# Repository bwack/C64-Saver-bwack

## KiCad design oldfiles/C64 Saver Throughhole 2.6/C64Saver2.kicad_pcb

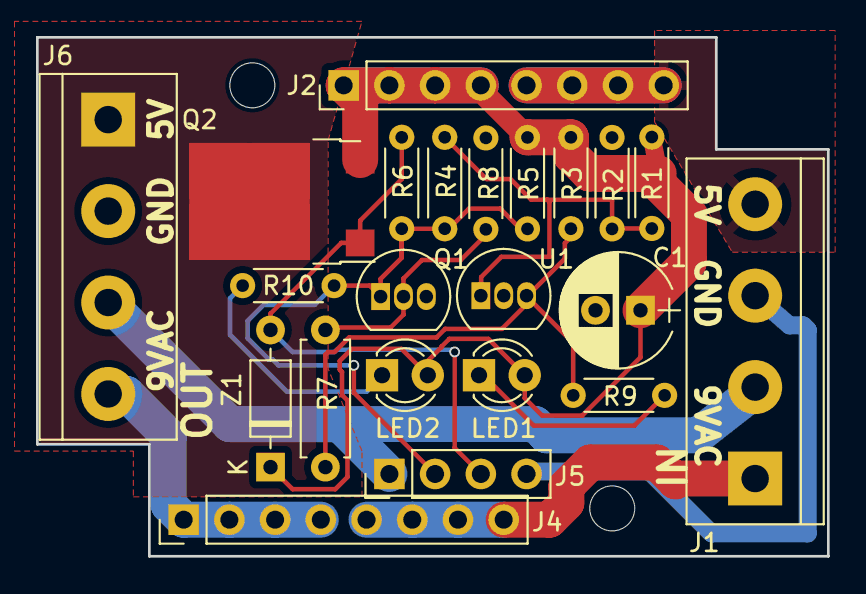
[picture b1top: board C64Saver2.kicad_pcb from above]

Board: 2 copper layers, 43.9 x 28.8 mm, 24 parts (0 on the bottom side), 14 nets.

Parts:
C1: 47uF; CP_Radial_D6.3mm_P2.50mm
J1, J6: Conn_01x04; TerminalBlock_bornier-4_P5.08mm
J2, J4: Conn_01x08; Pin_Header_Straight_1x08_Pitch2.54mm
J5: Conn_01x04; Pin_Header_Straight_1x04_Pitch2.54mm
LED1: 3mm RED; LED_D3.0mm
LED2: 3mm GREEN; LED_D3.0mm
MK1, MK2: Mounting_Hole; MountingHole_2.5mm
Q1: BC547; TO-92_Inline
Q2: IRFR5305; ATPAK-2
R1: 3k9 1%; R_Axial_DIN0204_L3.6mm_D1.6mm_P5.08mm_Horizontal
R2: 3k3 1%; R_Axial_DIN0204_L3.6mm_D1.6mm_P5.08mm_Horizontal
R3, R5: 3k3; R_Axial_DIN0204_L3.6mm_D1.6mm_P5.08mm_Horizontal
R4: 330k; R_Axial_DIN0204_L3.6mm_D1.6mm_P5.08mm_Horizontal
R6: 3k9; R_Axial_DIN0204_L3.6mm_D1.6mm_P5.08mm_Horizontal
R7: 33k; R_Axial_DIN0207_L6.3mm_D2.5mm_P7.62mm_Horizontal
R8: 10k; R_Axial_DIN0204_L3.6mm_D1.6mm_P5.08mm_Horizontal
R9, R10: 1k; R_Axial_DIN0204_L3.6mm_D1.6mm_P5.08mm_Horizontal
U1: TL431LP; TO-92_Inline
Z1: 6V8; D_DO-35_SOD27_P7.62mm_Horizontal

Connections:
/5V_SAFE: J6.1, Q2.2 (D)
/9VAC1: J1.1, J4.5, J4.6, J4.7, J4.8
/9VAC1': J4.1, J4.2, J4.3, J4.4, J6.4
/9VAC2: J1.2, J5.1, J6.3
/NGATE: Q1.2 (B), R7.2, R8.1
/SENSE: R1.2, R2.1, R4.1, U1.1 (REF)
/VCC1+: J1.4, J2.5, J2.6, J2.7, J2.8
/VCC1-: C1.1, J2.1, J2.2, J2.3, J2.4, LED1.2 (A), LED2.2 (A), Q2.3 (S), R1.1, R3.1, R5.1, Z1.1 (K)
GND: C1.2, J1.3, J5.4, J6.2, Q1.3 (E), R2.2, R8.2, U1.2 (A)
unnamed: LED1.1 (K), R9.1
unnamed: LED2.1 (K), R10.1
unnamed: R3.2, R7.1, R9.2, U1.3 (K)
OVERVOLTAGE: J5.2, Q1.1 (C), R4.2, R5.2, R6.2, R10.2
PGATE: J5.3, Q2.1 (G), R6.1, Z1.2 (A)

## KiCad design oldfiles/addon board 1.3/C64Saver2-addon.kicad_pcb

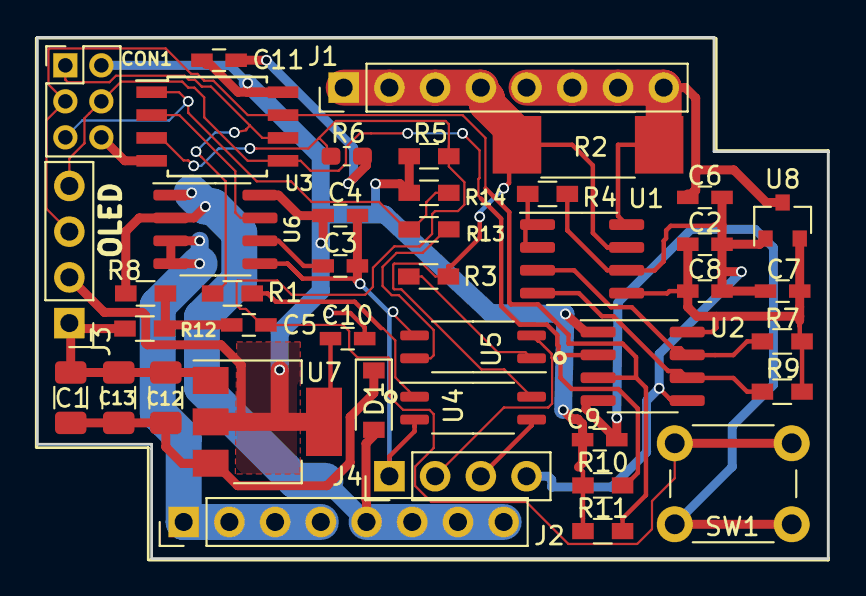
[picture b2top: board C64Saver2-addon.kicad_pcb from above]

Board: 2 copper layers, 43.9 x 29.0 mm, 42 parts (0 on the bottom side), 25 nets.

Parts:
C1, C12, C13: 47uF; C_1206_3216Metric
C2, C5, C8, C9, C11: 100n; C_0603_HandSoldering
C3, C6, C7, C10: 1u; C_0603_HandSoldering
C4: 100nF; C_0603_HandSoldering
CON1: AVR-ISP-6; Pin_Header_Straight_2x03_Pitch2.00mm
D1: Dotec SL1G; D_SOD-123
J1, J2: Conn_01x08_Female; Pin_Header_Straight_1x08_Pitch2.54mm
J3: OLED_128x32_Conn_01x04_Male; Pin_Header_Straight_1x04_Pitch2.54mm
J4: Conn_01x04_Female; Pin_Header_Straight_1x04_Pitch2.54mm
R1, R3: 560; R_0603_HandSoldering
R2: 0R1; R_2512_HandSoldering
R4: 10K; R_0603_HandSoldering
R5: 470k; R_0603_HandSoldering
R6: 470k; R_0603_1608Metric_Pad1.05x0.95mm_HandSolder
R7, R8, R9, R10, R11: 4k7; R_0603_HandSoldering
R12: 470; R_0603_HandSoldering
R13: 10k; R_0603_HandSoldering
R14: 1k; R_0603_HandSoldering
SW1: SW_Push; SW_PUSH_6mm_h13mm
U1: INA219xIDR-SOIC; SOIC-8_3.9x4.9mm_P1.27mm
U2: ISO1541D; SOIC-8_3.9x4.9mm_P1.27mm
U3: ATTINY85-20SU; SOIJ-8_5.3x5.3mm_P1.27mm
U4, U5: ACPL-217-50DE; SOIC-4_4.55x2.6mm_P1.27mm
U6: ACS712; SOIC-8_3.9x4.9mm_P1.27mm
U7: MCP1703; SOT-223-3_TabPin2
U8: MCP1703; SOT-23

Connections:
+5V: C4.2, C9.1, C10.2, C11.2, CON1.2, J3.2, R5.2, R10.2, R11.2, R14.2, U2.1, U3.8, U6.8, U7.2
/9VAC1+: D1.2, J2.5, J2.6, J2.7, J2.8, R8.2, U6.1, U6.2
/9VAC1-: J2.1, J2.2, J2.3, J2.4, U6.3, U6.4
/#OVERVOLTAGE: CON1.5, R13.1, R14.1, U3.1
/FILTER: C3.2, U6.6
/HOLD: R1.2, U4.1
/HOLD_: CON1.1, R1.1, U3.6
/SCL1: CON1.3, J3.3, R11.1, U2.3, U3.7
/SCL2: R9.1, U1.4, U2.6
/SDA1: CON1.4, J3.4, R10.1, U2.2, U3.5
/SDA2: R7.1, U1.3, U2.7
/SENSE_ACCUR: U3.2, U6.7
/SENSE_VAC: C5.2, R5.1, R6.2, SW1.2, U3.3
/VDD2: C2.1, C7.2, C8.1, R7.2, R9.2, U1.5, U2.8, U8.2
/VIN+: C6.2, J1.5, J1.6, J1.7, J1.8, R2.2, U1.8, U8.3
GND: C1.2, C3.1, C4.1, C9.2, C10.1, C11.1, C12.2, C13.2, CON1.6, J3.1, J4.1, R6.1, R12.1, SW1.1, U2.4, U3.4, U4.2, U5.3, U6.5, U7.1
GNDD: C2.2, C6.1, C7.1, C8.2, J4.4, R4.1, U1.6, U2.5, U8.1
unnamed: C1.1, C12.1, C13.1, D1.1, U7.3
unnamed: C5.1, R8.1, R12.2
unnamed: R3.1, U5.1
unnamed: R4.2, U1.1, U1.2
unnamed: R13.2, U5.4
OVERVOLTAGE: J4.2, U5.2
PGATE: J4.3, U4.3
VIN-: J1.1, J1.2, J1.3, J1.4, R2.1, R3.2, U1.7, U4.4

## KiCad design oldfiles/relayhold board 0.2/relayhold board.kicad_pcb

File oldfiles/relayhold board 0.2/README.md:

# The C64 Saver 2 relay hold board

The addon board is for many hard to make. I was thinking, what about making a board that doesn't need to be programmed, that can cut 9VAC, and optionally keep the outputs disabled even if the fault goes away. This circuit is it. It was more of an experimental circuit. I've therefor archived it here.

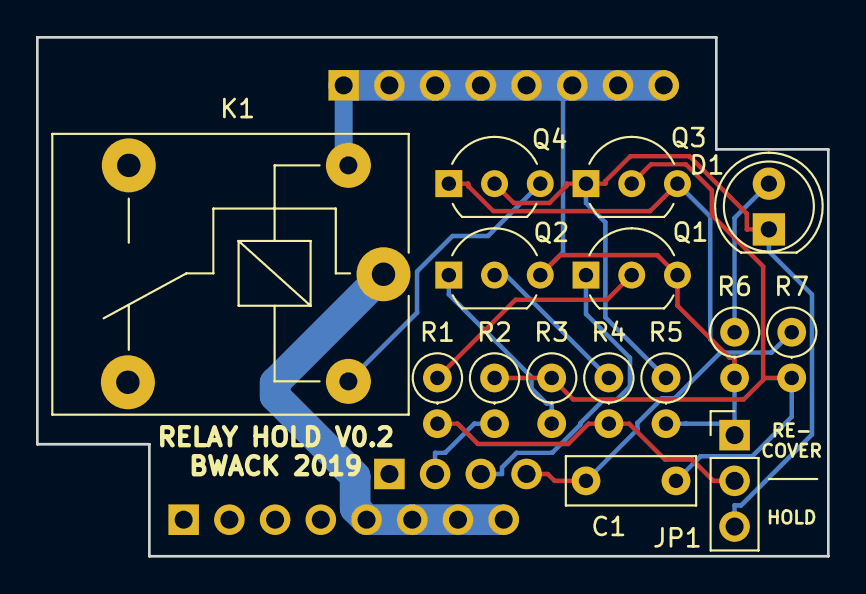
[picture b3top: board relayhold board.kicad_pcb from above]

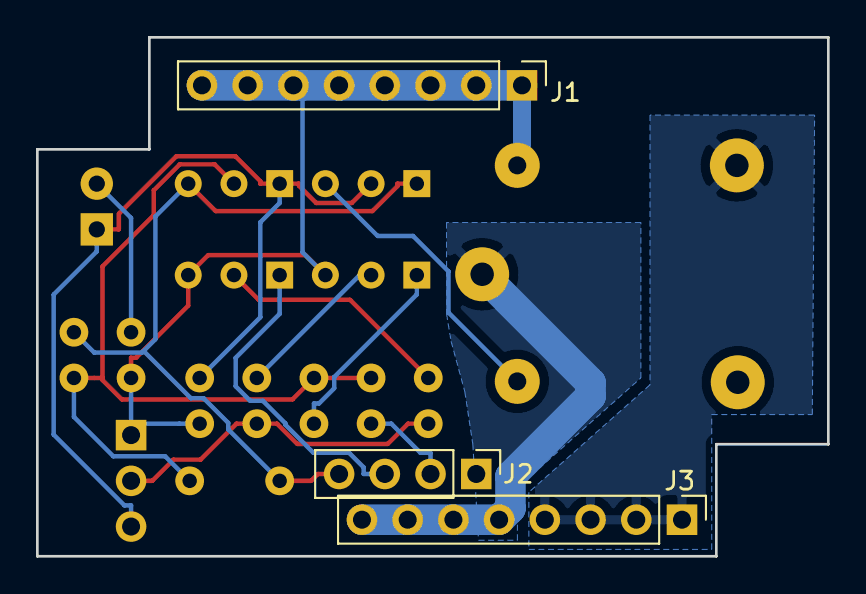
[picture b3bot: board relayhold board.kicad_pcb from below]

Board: 2 copper layers, 43.9 x 28.8 mm, 18 parts (3 on the bottom side), 14 nets.

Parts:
C1: 1u; C_Rect_L7.0mm_W2.5mm_P5.00mm
D1: RED_LED; LED_D5.0mm
J1, J3: Conn_01x08; PinHeader_1x08_P2.54mm_Vertical
J2: Conn_01x04; PinHeader_1x04_P2.54mm_Vertical
JP1: Jumper_3_Open; PinHeader_1x03_P2.54mm_Vertical
K1: SANYOU_SRD_Form_C; Relay_SPDT_SANYOU_SRD_Series_Form_C
Q1, Q2: Q_PNP_BCE; TO-92_Inline_Wide
Q3: BC337; TO-92_Inline_Wide
Q4: 2N7000; TO-92_Inline_Wide
R1, R2, R4: 100K; R_Axial_DIN0207_L6.3mm_D2.5mm_P2.54mm_Vertical
R3: 1K; R_Axial_DIN0207_L6.3mm_D2.5mm_P2.54mm_Vertical
R5, R7: 33K; R_Axial_DIN0207_L6.3mm_D2.5mm_P2.54mm_Vertical
R6: 560; R_Axial_DIN0207_L6.3mm_D2.5mm_P2.54mm_Vertical

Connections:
/9VAC1: J3.5, J3.6, J3.7, J3.8, K1.1
/9VAC1': J3.1, J3.2, J3.3, J3.4, K1.3
/MOSFET_GATE: D1.1, JP1.3, Q3.1, Q4.2, R5.1
/OVERVOLTAGE: J2.2, R2.2
/OV_GATE: C1.1, Q3.2, R2.1, R3.1, R7.2
/PGATE: J2.3, Q1.1
/V_IN: J1.1, J1.2, J1.3, J1.4, J1.5, J1.6, J1.7, J1.8, JP1.1, K1.2, Q1.3, Q2.3, R5.2, R6.2
GND: C1.2, J2.4, Q3.3, Q4.1, R7.1
unnamed: D1.2, R6.1
unnamed: JP1.2, R1.2, R4.2
unnamed: K1.5, Q4.3
unnamed: Q1.2, R1.1
unnamed: Q2.1, R3.2
unnamed: Q2.2, R4.1
